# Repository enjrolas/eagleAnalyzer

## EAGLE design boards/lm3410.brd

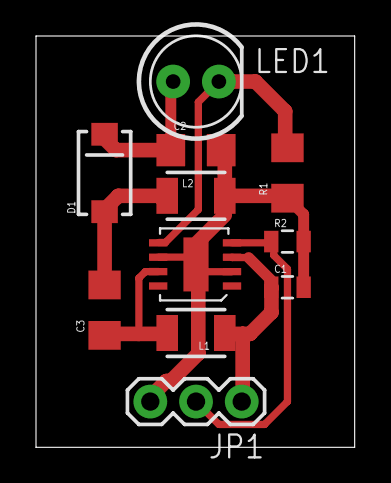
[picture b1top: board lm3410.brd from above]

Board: 2 copper layers, 17.7 x 22.9 mm, 11 parts (0 on the bottom side), 7 nets.

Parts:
C1: 10uF; 0805
C2: 10uF; 1206
C3: 2.2uF; 1206
D1: DIODE-SCHOTTKY_; SMA-DIODE
JP1: 1X03
L1, L2: 4.7uH; 1210
LED1: LED5MM
R1: 0.2; 1206
R2: 100k; 0805
U$1: LM3410-MSOP-8; MSOP-8

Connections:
DIM: JP1.2, R2.1, U$1.4
GND: C1.2, C2.2, JP1.3, L2.2, R1.1, R2.2, U$1.2, U$1.6, U$1.9
unnamed: LED1.K, R1.2, U$1.5
unnamed: C3.1, L1.2, U$1.7
unnamed: C3.2, D1.A, L2.1
unnamed: C2.1, D1.C, LED1.A
VCC: C1.1, JP1.1, L1.1, U$1.3

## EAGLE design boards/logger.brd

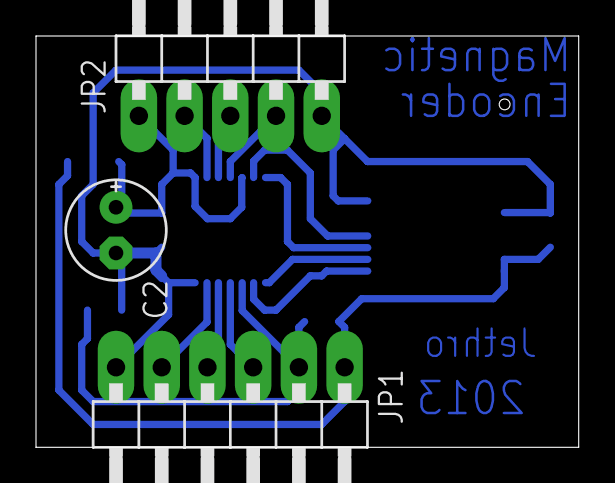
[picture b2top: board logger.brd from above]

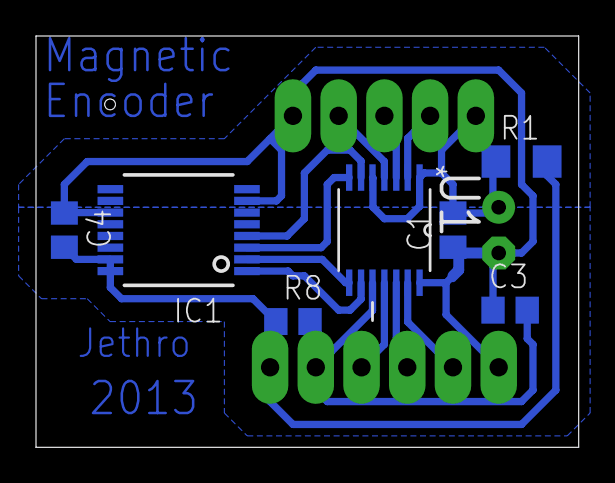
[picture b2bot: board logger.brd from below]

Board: 2 copper layers, 30.2 x 22.9 mm, 10 parts (7 on the bottom side), 14 nets.

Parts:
C1, C3, C4: C0805
C2: E2,5-6E
IC1: AS5040; SSOP16
JP1: 1X06/90
JP2: 1X05/90
R1: R1206
R8: R0805
U1: MSP430G2352IPW14; SOP65P640X120-14N

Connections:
+3V3: C1.2, C2.+, JP2.1, R1.1, U1.1, U1.5
GND: C1.1, C2.-, C3.1, C4.1, IC1.7, IC1.11, JP1.6, JP2.5, U1.14
unnamed: JP1.3, U1.11
unnamed: JP2.3, U1.3
unnamed: JP1.4, U1.12
unnamed: IC1.4, U1.6
unnamed: IC1.3, U1.7
unnamed: C4.2, IC1.15, IC1.16, JP1.1, R1.2, R8.1
unnamed: JP1.5, U1.13
unnamed: IC1.2, U1.8
unnamed: IC1.1, U1.9
unnamed: JP2.2, U1.2
unnamed: C3.2, JP1.2, R8.2, U1.10
unnamed: JP2.4, U1.4

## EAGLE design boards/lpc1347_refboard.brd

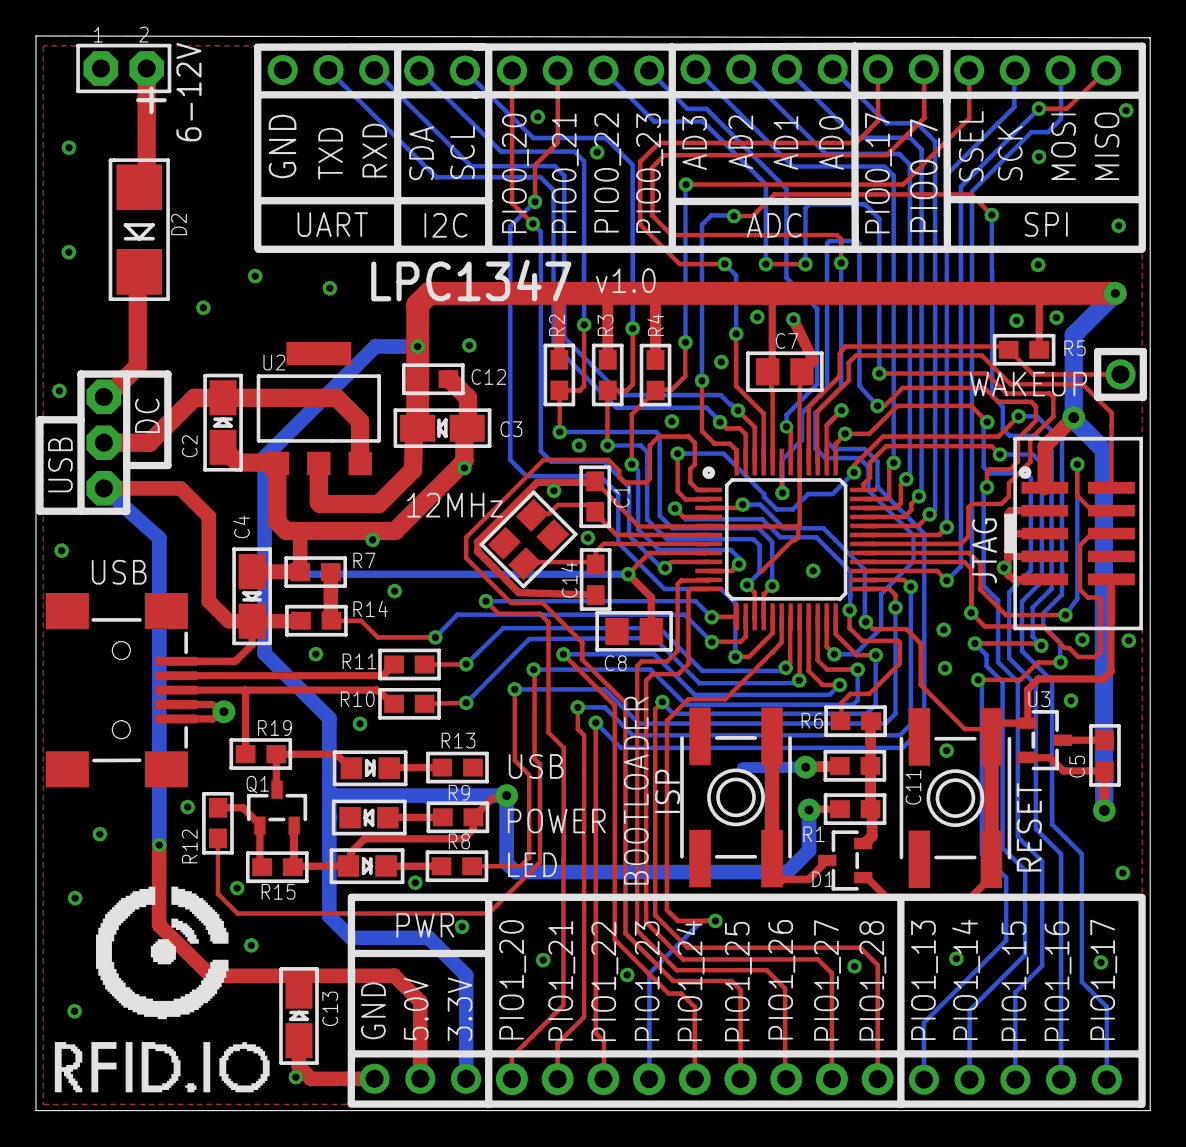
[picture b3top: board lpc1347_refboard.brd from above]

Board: 2 copper layers, 61.9 x 59.7 mm, 54 parts (0 on the bottom side), 59 nets.

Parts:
BTN1: Reset; EVQ-Q2
BTN2: ISP; EVQ-Q2
C1, C14: 16pF; 0603
C2, C3, C4, C13: 10µF; EIA3216-18/A-R
C5, C11, C12: 0.1µF; 0603
C7, C8: 10µF; 0805
CN1: USBMINIB; USB-MINIB
D1: BAT54C; SOT23-R
D2: MULTICOMPSS12; SMADIODE
JP1: PWR; 1X03_ROUND
JP2: ADC; 1X04_ROUND
JP3: SPI; 1X04_ROUND
JP4: I2C; 1X02_ROUND
JP5: UART; 1X03_ROUND
JP6: WAKEUP; 1X01_ROUND
JP7: 1X04_ROUND
JP9: 1X05_ROUND
JP10: JUMPER2
JP11: 1X09_ROUND_70
JP12: POWERSOURCE; JUMPER3
JP13: 1X02_ROUND
JTAG1: JTAG; 2X05_1.27MM_SMT
LED1: POWER; CHIPLED_0805
LED2: 2mA; CHIPLED_0805
LED3: USB; CHIPLED_0805
Q1: MMBT2907A; SOT23-R
R1: 20K; 0603
R2, R3, R4, R5, R14, R15: 10K; 0603
R6: 1K; 0603
R7: 100K; 0603
R8: 1.0K; 0603
R9, R13: 150; 0603
R10, R11: 33; 0603
R12: 2K; 0603
R19: 1.5K; 0603
U2: LM1117(3.3); SOT223-R
U3: MCP130T; SOT23-R
U4: LPC1347FBD48; LQFP48
U$23: RFID_IO_LOGO_1X1
Y2: 12MHz; CRYSTAL_3.2X2.5

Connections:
3.3V: C3.+, C5.1, C7.1, C8.1, C12.1, JP1.1, JTAG1.1, LED2.A, Q1.2, R1.2, R2.2, R3.2, R4.2, R5.2, R9.1, R15.1, U2.2, U3.2, U4.8, U4.44
5.0V: C4.+, C13.+, CN1.VBUS, JP1.2, JP12.1, R14.1
GND: BTN1.A, BTN1.A', BTN2.A, BTN2.A', C1.1, C2.-, C3.-, C4.-, C5.2, C7.2, C8.2, C11.2, C12.2, C13.-, C14.1, CN1.GND, CN1.ID, JP1.3, JP5.1, JP10.1, JTAG1.3, JTAG1.5, JTAG1.7, JTAG1.9, LED1.C, R7.1, R13.1, U2.1, U3.3, U4.5, U4.41
unnamed: LED2.C, R8.1
unnamed: C2.+, JP12.2, U2.3
unnamed: D2.A, JP10.2
unnamed: BTN2.B, BTN2.B', D1.3
unnamed: CN1.D+, R10.1, R19.2
unnamed: Q1.1, R12.1, R15.2
unnamed: C11.1, D1.2, R1.1, R6.1
unnamed: LED1.A, R9.2
unnamed: LED3.C, R13.2
unnamed: CN1.D-, R11.1
unnamed: LED3.A, Q1.3, R19.1
PIO0_0/RESET: BTN1.B, BTN1.B', D1.1, JTAG1.10, U3.1, U4.3
PIO0_1/ISP: R6.2, U4.4
PIO0_2/SSEL: JP3.4, R4.1, U4.10
PIO0_3/USBVBUS: R7.2, R14.2, U4.14
PIO0_4/SCL: JP4.1, R3.1, U4.15
PIO0_5/SDA: JP4.2, R2.1, U4.16
PIO0_6/USBCONNECT: R12.2, U4.22
PIO0_7: JP13.2, U4.23
PIO0_8/MISO: JP3.1, U4.27
PIO0_9/MOSI/SWO: JP3.2, JTAG1.6, U4.28
PIO0_10/SWCLK: JTAG1.4, U4.29
PIO0_11/AD0: JP2.1, U4.32
PIO0_12/AD1: JP2.2, U4.33
PIO0_13/AD2: JP2.3, U4.34
PIO0_14/AD3: JP2.4, U4.35
PIO0_15/SWDIO: JTAG1.2, U4.39
PIO0_16/WAKEUP: JP6.1, R5.1, U4.40
PIO0_17: JP13.1, U4.45
PIO0_18/RXD: JP5.3, U4.46
PIO0_19/TXD: JP5.2, U4.47
PIO0_20: JP7.4, U4.9
PIO0_21: JP7.3, U4.17
PIO0_22: JP7.2, U4.30
PIO0_23: JP7.1, U4.42
PIO1_13: JP9.1, U4.36
PIO1_14: JP9.2, U4.37
PIO1_15: JP9.3, U4.43
PIO1_16: JP9.4, U4.48
PIO1_19: JP9.5, U4.2
PIO1_20: JP11.1, U4.13
PIO1_21: JP11.2, U4.26
PIO1_22: JP11.3, U4.38
PIO1_23: JP11.4, U4.18
PIO1_24: JP11.5, U4.21
PIO1_25: JP11.6, U4.1
PIO1_26: JP11.7, U4.11
PIO1_27: JP11.8, U4.12
PIO1_28: JP11.9, U4.24
PIO1_29/SCK: JP3.3, U4.31
PIO1_31/LED: R8.2, U4.25
USBD+: R10.2, U4.20
USBD-: R11.2, U4.19
VCC: D2.C, JP12.3
XTALIN: C1.2, U4.6, Y2.2
XTALOUT: C14.2, U4.7, Y2.1

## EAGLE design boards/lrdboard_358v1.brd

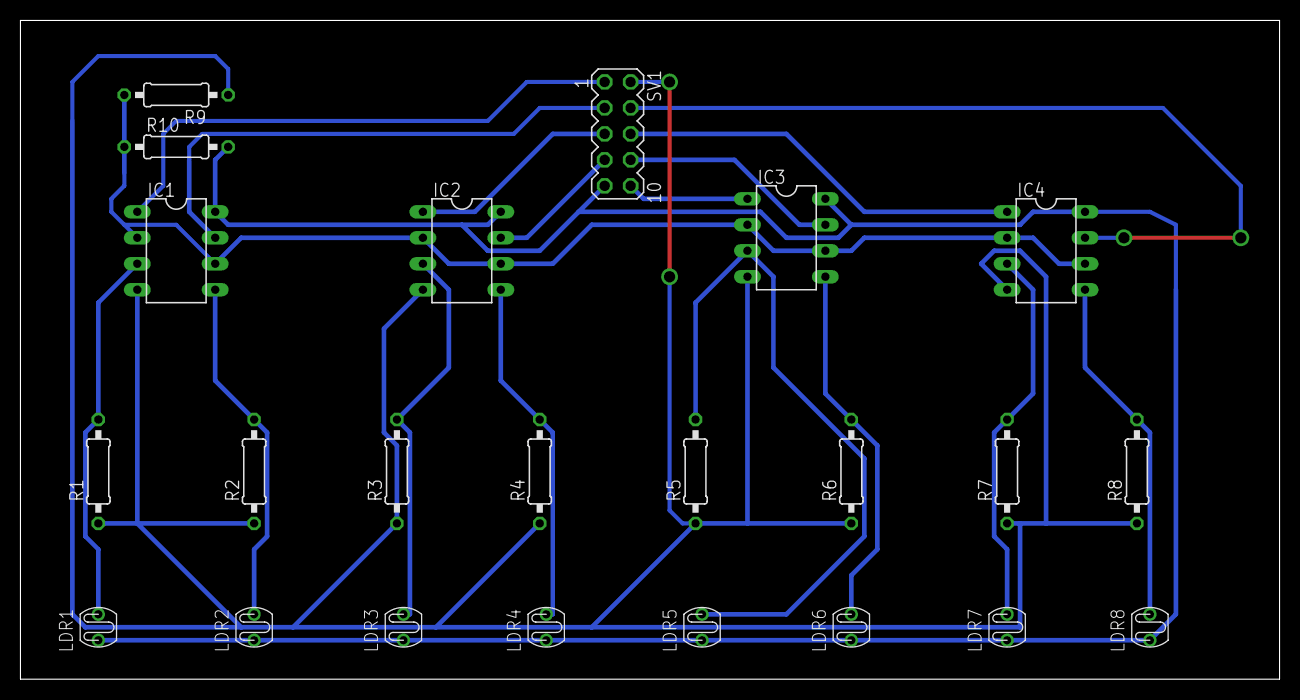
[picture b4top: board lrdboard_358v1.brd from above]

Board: 2 copper layers, 123.2 x 64.4 mm, 23 parts (0 on the bottom side), 19 nets.

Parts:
IC1, IC2, IC3, IC4: LM358N; DIL08
LDR1, LDR2, LDR3, LDR4, LDR5, LDR6, LDR7, LDR8: CDSLDR3MM; LDR3MM
R1, R2, R3, R4, R5, R6, R7, R8, R9, R10: 0207/10
SV1: MA05-2

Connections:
1: IC1.3, LDR1.P$2, R1.2
2: IC1.5, LDR2.P$2, R2.2
3: IC2.3, LDR3.P$2, R3.2
4: IC2.5, LDR4.P$2, R4.2
5: IC3.3, LDR5.P$2, R5.2
6: IC3.5, LDR6.P$2, R6.2
7: IC4.3, LDR7.P$2, R7.2
8: IC4.5, LDR8.P$2, R8.2
+5V: IC1.8, IC2.8, IC3.8, IC4.8, LDR1.P$1, LDR2.P$1, LDR3.P$1, LDR4.P$1, LDR5.P$1, LDR6.P$1, LDR7.P$1, LDR8.P$1, R10.2, SV1.9
GND: IC1.4, IC2.4, IC3.4, IC4.4, R1.1, R2.1, R3.1, R4.1, R5.1, R6.1, R7.1, R8.1, R9.1, SV1.2
MID: IC1.2, IC1.6, IC2.2, IC2.6, IC3.2, IC3.6, IC4.2, IC4.6, R9.2, R10.1
OUT1: IC1.1, SV1.1
OUT2: IC1.7, SV1.3
OUT3: IC2.1, SV1.5
OUT4: IC2.7, SV1.7
OUT5: IC3.1, SV1.10
OUT6: IC3.7, SV1.8
OUT7: IC4.1, SV1.6
OUT8: IC4.7, SV1.4

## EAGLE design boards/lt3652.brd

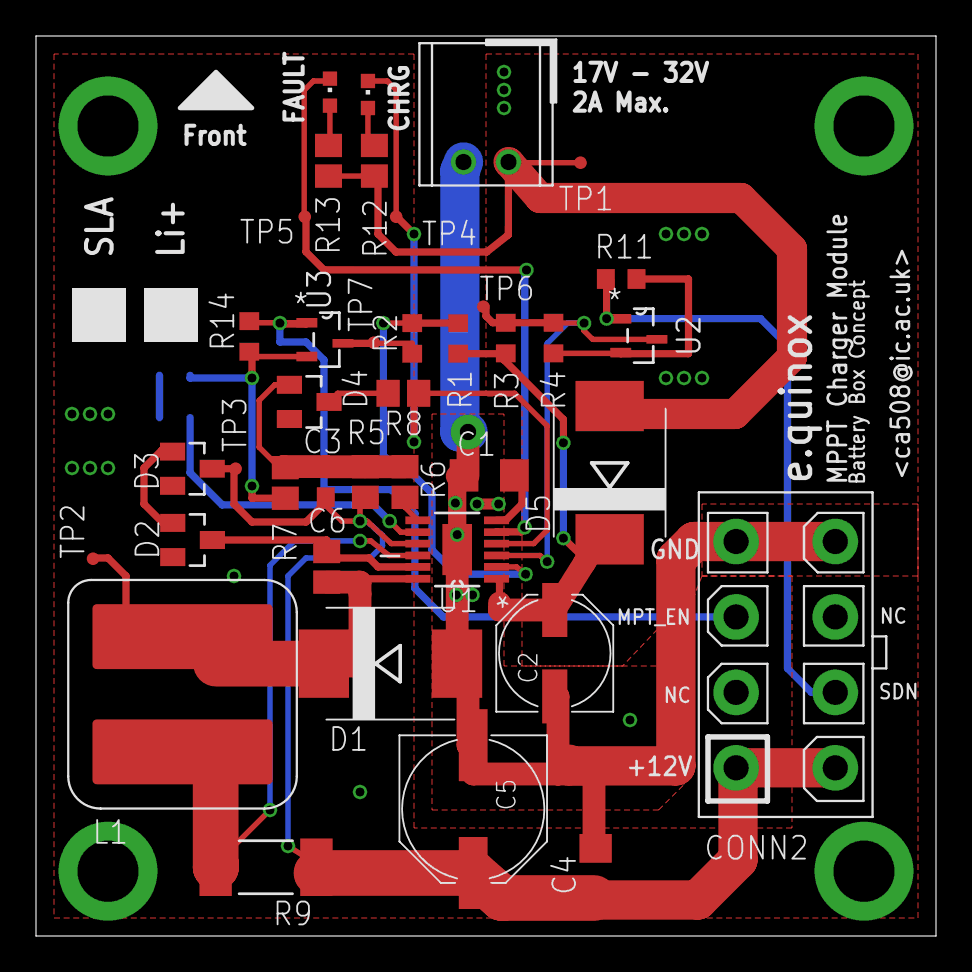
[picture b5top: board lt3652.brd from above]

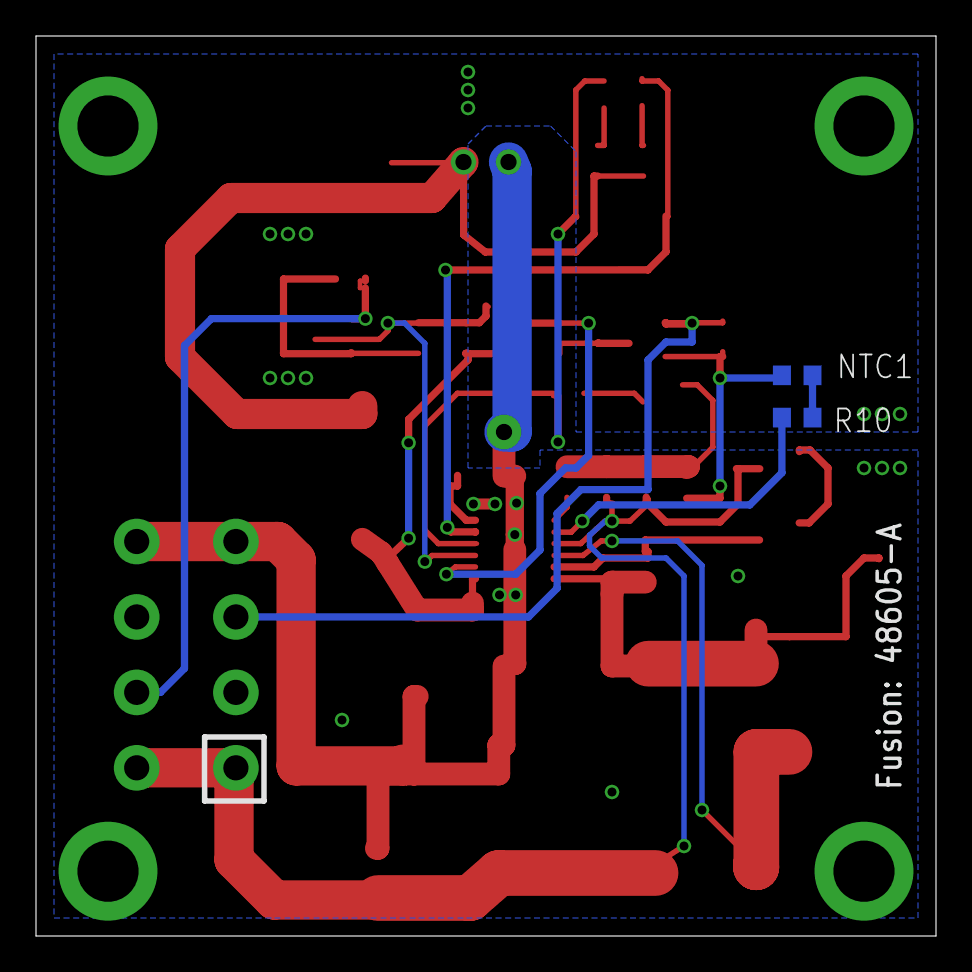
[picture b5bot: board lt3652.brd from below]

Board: 2 copper layers, 50.0 x 50.0 mm, 41 parts (2 on the bottom side), 23 nets.

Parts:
C1: 4.7uF; C1206
C2: 33uF; PANASONIC_D
C3: 50pF; C0603
C4: 10uF; C1206
C5: 100uF; PANASONIC_F
C6: 1uF; C0805
CONN1: 22-05-7025
CONN2: 39-28-1083
D1, D5: MBRS340T3; SMC
D2: PMBD914; SOT23
D3: BZX84C6V2L; SOT23
D4: BAW56; SOT23
L1: SDR1006-220ML; SDR1006
LED1: GREEN; CHIPLED_0603
LED2: RED; CHIPLED_0603
NTC1: 10k; R0603
R1: 499k; R0603
R2: 100k; R0603
R3: 0; R0603
R4: DNP; R0603
R5: 309k; R0805
R6: 174k; R0805
R7: 100k; R0805
R8: 1M; R0805
R9: 0.06; R2512
R10: 910; R0603
R11, R14: 2.7k; R0603
R12, R13: 4.7k; R0805
TP1, TP2, TP3, TP4, TP5, TP6, TP7: TPTP07R; TP07R
U1: LT3652EMSEPBF; SOP65P490X110-13N
U2, U3: 2N7002E; SOT95P230X110-3N

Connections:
0V: C1.2, C2.-, C4.2, C5.-, CONN1.2, CONN2.P$4, CONN2.P$8, D1.A, NTC1.1, R4.1, R7.2, R11.1, R14.1, U1.13, U2.2, U3.2
!CHRG: LED1.C, R8.2, TP4.TP, U1.4
!MPPT!: R2.1, TP7.TP, U3.3
!SHDN!: R3.1, R4.2, TP6.TP, U1.3, U2.3
+12V: C3.1, C4.1, C5.+, CONN2.P$1, CONN2.P$5, D3.3, R5.2, R9.1, TP3.TP, U1.9
CHG_VIN: C2.+, D5.C, R1.2, R3.2, U1.1
MPPT_EN: CONN2.P$3, R14.2, U3.1
unnamed: R1.1, R2.2, U1.2
unnamed: C6.2, D1.C, L1.P$1, TP2.TP, U1.12
unnamed: C1.1, U1.6
unnamed: C6.1, D2.3, U1.11
unnamed: R10.2, U1.8
unnamed: D2.1, D3.1
unnamed: L1.P$2, R9.2, U1.10
unnamed: C3.2, D4.1, R5.1, R6.1, R7.1
unnamed: D4.3, R8.1
unnamed: LED2.C, TP5.TP, U1.5
unnamed: NTC1.2, R10.1
unnamed: LED1.A, R12.1
unnamed: LED2.A, R13.1
SHDN: CONN2.P$6, R11.2, U2.1
VCC: CONN1.1, D5.A, R12.2, R13.2, TP1.TP
VFB: R6.2, U1.7

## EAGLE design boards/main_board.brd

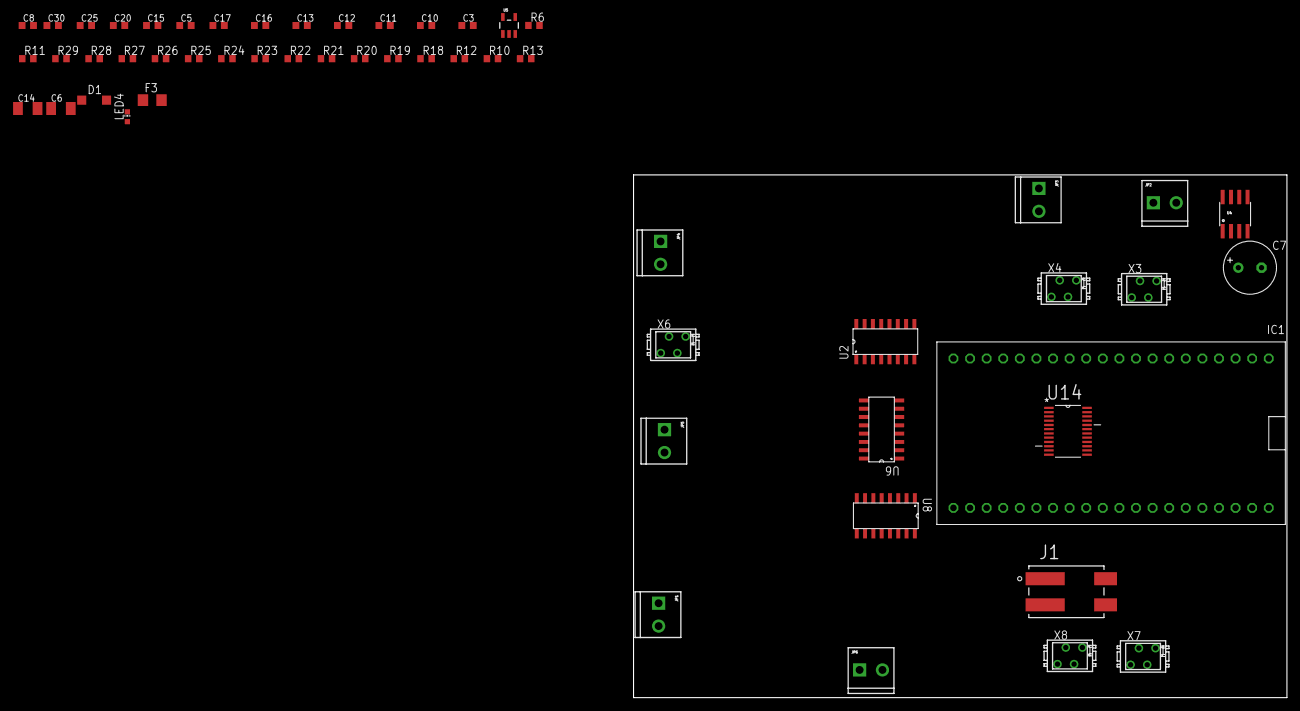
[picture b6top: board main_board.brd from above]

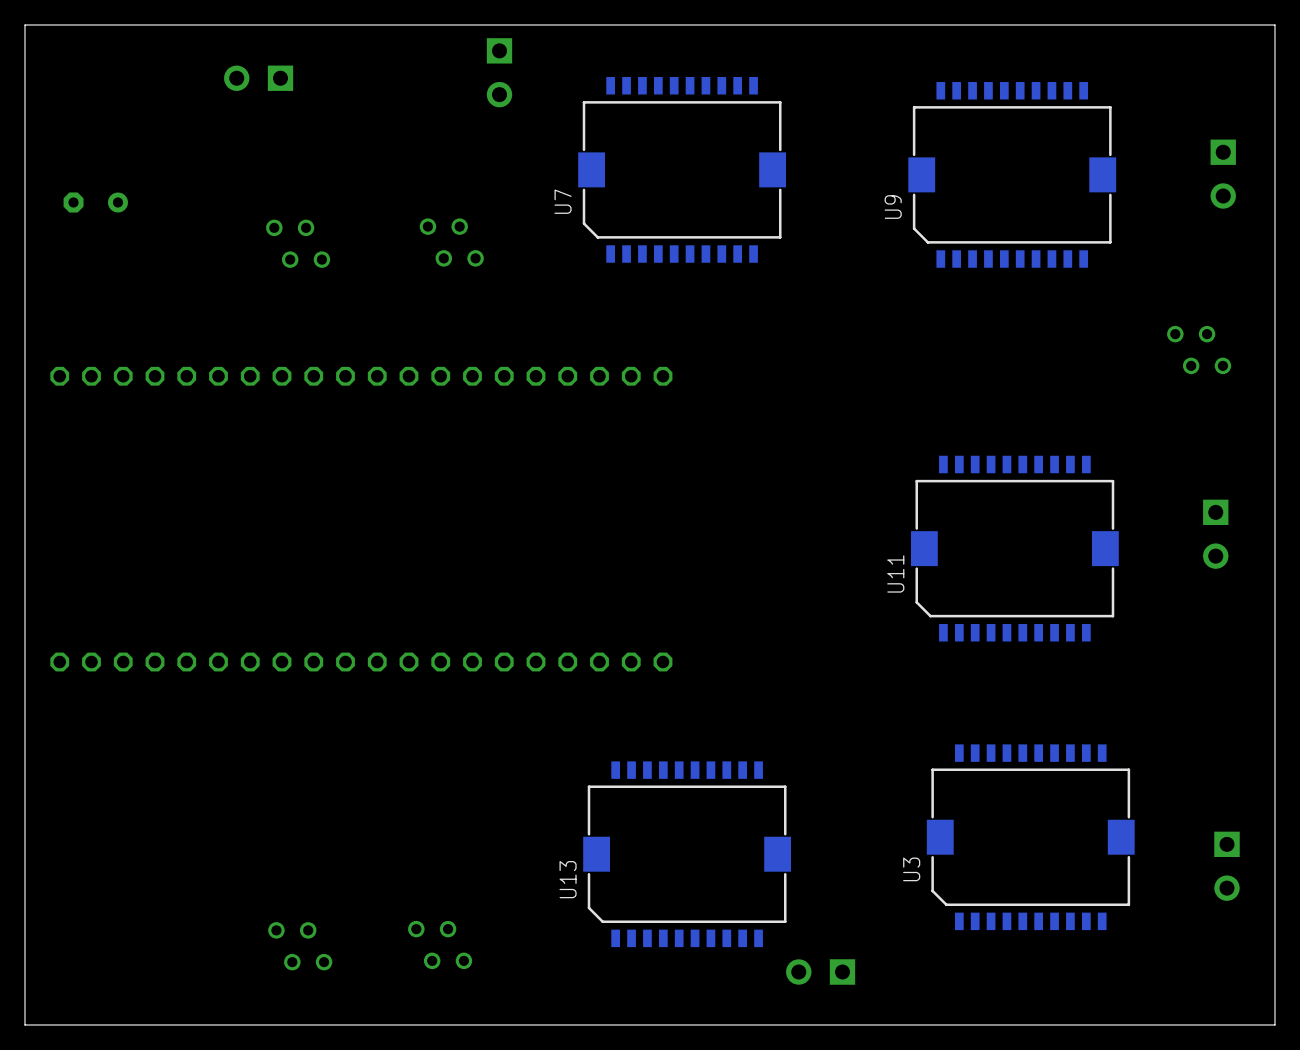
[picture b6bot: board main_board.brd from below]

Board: 2 copper layers, 100.0 x 80.0 mm, 60 parts (5 on the bottom side), 83 nets, no tracks yet.

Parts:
C3, C10, C11, C12, C13, C16, C17: 100nF; C0603K
C5, C15, C20, C25, C30: 33nF; C0603K
C6, C14: 10uF; C1206K
C7: 470uF-16V; E3,5-8
C8: 1uF; C0603K
D1: 12V; SOD123
F3: FUSE_5A; R1206
IC1: MBED_MICROCONTROLLER; DIL40_0.9
J1: 2060-402; WAGO_2060-402
JP1, JP3, JP4, JP5, JP6: MOTOR; SCREWTERMINAL-3.5MM-2
JP2: PWR; SCREWTERMINAL-3.5MM-2
LED4: CHIP-LED0603
R6: 1k; R0603
R10, R11, R12, R18, R19, R20, R21, R22, R23, R24, R25, R26, R27, R28, R29: 10k; R0603
R13: 100k; R0603
U2, U6, U8: SI8460AA-B-IS1; SOIC-16
U3, U7, U9, U11, U13: MC33887-HSOP; HSOP
U4: NFET-SOIC8; SO08
U5: LDO; SOT23-5
U14: PCF8575PWE4; SOP65P640X120-24N
X3: ENC1; MICROMATCH-4
X4: ENC2; MICROMATCH-4
X6: ENC3; MICROMATCH-4
X7: ENC4; MICROMATCH-4
X8: ENC5; MICROMATCH-4

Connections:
+3V3: IC1.40, U14.24
+5V: C6.1, C11.1, C13.1, C17.1, R6.2, R11.2, R12.2, R19.2, R20.2, R22.2, R23.2, R25.2, R26.2, R28.2, R29.2, U2.16, U5.5, U6.16, U8.16
+12V: C8.1, F3.1, U3.4, U3.5, U3.16, U5.1, U5.3, U7.4, U7.5, U7.16, U9.4, U9.5, U9.16, U11.4, U11.5, U11.16, U13.4, U13.5, U13.16
DIR1_1: U2.3, U14.4
DIR1_1_D: U2.14, U3.3
DIR1_2: U2.4, U14.5
DIR1_2_D: U2.13, U3.19
DIR2_1: U2.6, U14.6
DIR2_1_D: U2.11, U7.3
DIR2_2: U2.7, U14.7
DIR2_2_D: U2.10, U7.19
DIR3_1: U6.3, U14.8
DIR3_1_D: U6.14, U9.3
DIR3_2: U6.4, U14.9
DIR3_2_D: U6.13, U9.19
DIR4_1: U6.6, U14.10
DIR4_1_D: U6.11, U11.3
DIR4_2: U6.7, U14.11
DIR4_2_D: U6.10, U11.19
DIR5_1: U8.3, U14.13
DIR5_1_D: U8.14, U13.3
DIR5_2: U8.4, U14.14
DIR5_2_D: U8.13, U13.19
ENC1A: IC1.8, X3.3
ENC1B: IC1.11, X3.4
ENC2A: IC1.12, X4.3
ENC2B: IC1.15, X4.4
ENC3A: IC1.16, X6.3
ENC3B: IC1.17, X6.4
ENC4A: IC1.18, X7.3
ENC4B: IC1.26, X7.4
ENC5A: IC1.27, X8.3
ENC5B: IC1.28, X8.4
EXTEND_SCL: IC1.10, U14.22
EXTEND_SDA: IC1.9, U14.23
FAUL1T_D: R12.1, U3.2
FAULT1_D: R20.1, U7.2
FAULT3_D: R23.1, U9.2
FAULT4_D: R26.1, U11.2
FAULT5_D: R29.1, U13.2
GND: C10.2, C12.2, C16.2, IC1.1, U2.8, U6.8, U8.8, U14.2, U14.3, U14.12, U14.21, X3.1, X4.1, X6.1, X7.1, X8.1
GNDA: C3.2, C5.2, C6.2, C7.-, C8.2, C11.2, C13.2, C14.2, C15.2, C17.2, C20.2, C25.2, C30.2, D1.A, LED4.C, R10.1, R18.1, R21.1, R24.1, R27.1, U2.9, U3.1, U3.9, U3.10, U3.11, U3.12, U3.SL1, U3.SL2, U4.1, U4.2, U4.3, U5.2, U6.9, U7.1, U7.9, U7.10, U7.11, U7.12, U7.SL1, U7.SL2, U8.9, U9.1, U9.9, U9.10, U9.11, U9.12, U9.SL1, U9.SL2, U11.1, U11.9, U11.10, U11.11, U11.12, U11.SL1, U11.SL2, U13.1, U13.9, U13.10, U13.11, U13.12, U13.SL1, U13.SL2
unnamed: C3.1, U5.4
unnamed: LED4.A, R6.1
unnamed: C5.1, U3.17
unnamed: R11.1, U3.20
unnamed: R10.2, U3.18
unnamed: D1.C, R13.1, U4.4
unnamed: JP2.1, U4.5, U4.6, U4.7, U4.8
unnamed: JP1.2, U3.6, U3.7
unnamed: JP1.1, U3.14, U3.15
unnamed: C7.+, C14.1, F3.2, JP2.2, R13.2
unnamed: C15.1, U7.17
unnamed: R19.1, U7.20
unnamed: R18.2, U7.18
unnamed: JP3.2, U7.6, U7.7
unnamed: JP3.1, U7.14, U7.15
unnamed: C20.1, U9.17
unnamed: R22.1, U9.20
unnamed: R21.2, U9.18
unnamed: JP4.2, U9.6, U9.7
unnamed: JP4.1, U9.14, U9.15
unnamed: C25.1, U11.17
unnamed: R25.1, U11.20
unnamed: R24.2, U11.18
unnamed: JP5.2, U11.6, U11.7
unnamed: JP5.1, U11.14, U11.15
unnamed: C30.1, U13.17
unnamed: R28.1, U13.20
unnamed: R27.2, U13.18
unnamed: JP6.2, U13.6, U13.7
unnamed: JP6.1, U13.14, U13.15
PWM1: IC1.21, U2.2
PWM1_D: U2.15, U3.13
PWM2: IC1.22, U2.5
PWM2_D: U2.12, U7.13
PWM3: IC1.23, U6.2
PWM3_D: U6.15, U9.13
PWM4: IC1.24, U6.5
PWM4_D: U6.12, U11.13
PWM5: IC1.25, U8.2
PWM5_D: U8.15, U13.13
VCC: C10.1, C12.1, C16.1, IC1.2, U2.1, U6.1, U8.1, X3.2, X4.2, X6.2, X7.2, X8.2

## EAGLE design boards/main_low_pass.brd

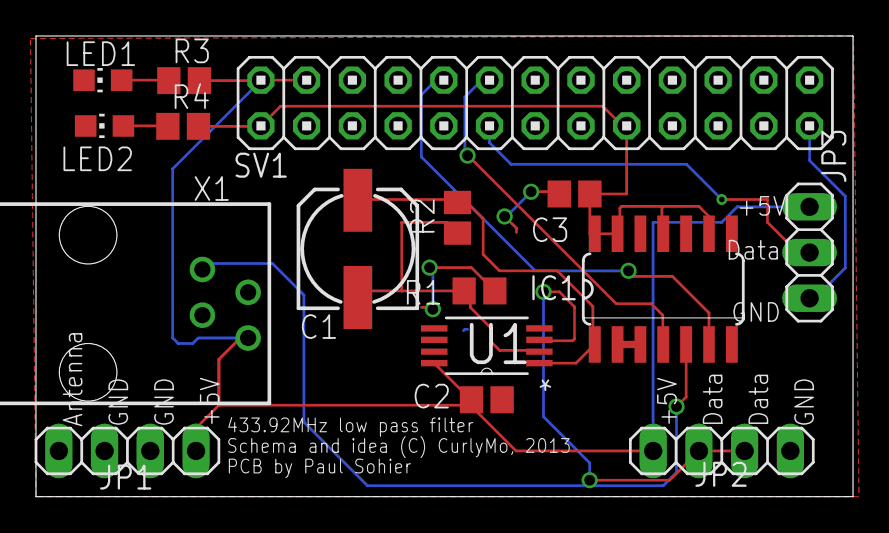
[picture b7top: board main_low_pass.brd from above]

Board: 2 copper layers, 45.4 x 25.6 mm, 16 parts (0 on the bottom side), 13 nets.

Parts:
C1: 15u; 153CLV-0605
C2, C3: C0805
IC1: 74HC14D; SO14
JP1, JP2: 1X04
JP3: 1X03
LED1, LED2: CHIP-LED0805
R1, R2, R3, R4: R0805
SV1: 2X13
U1: SOP65P640X120-8N
X1: 14867

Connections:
GND: C2.2, C3.2, IC1.7, JP1.2, JP1.3, JP2.4, JP3.1, LED1.C, LED2.C, R1.1, SV1.6, SV1.9, SV1.14, SV1.20, SV1.25, U1.4, X1.3
unnamed: JP2.2, JP2.3, U1.3
unnamed: C1.-, R1.2, R2.1, U1.2
unnamed: IC1.2, IC1.3
unnamed: IC1.5, X1.1
unnamed: JP3.2, SV1.11
unnamed: C2.1, JP1.4, JP2.1, JP3.3, R3.2, SV1.2, SV1.4, U1.8, X1.4
unnamed: C1.+, IC1.1, R2.2, U1.1
unnamed: LED1.A, R3.1
unnamed: LED2.A, R4.1
unnamed: IC1.4, SV1.12
unnamed: IC1.6, SV1.10
VCC: C3.1, IC1.9, IC1.11, IC1.13, IC1.14, R4.2, SV1.1, SV1.17

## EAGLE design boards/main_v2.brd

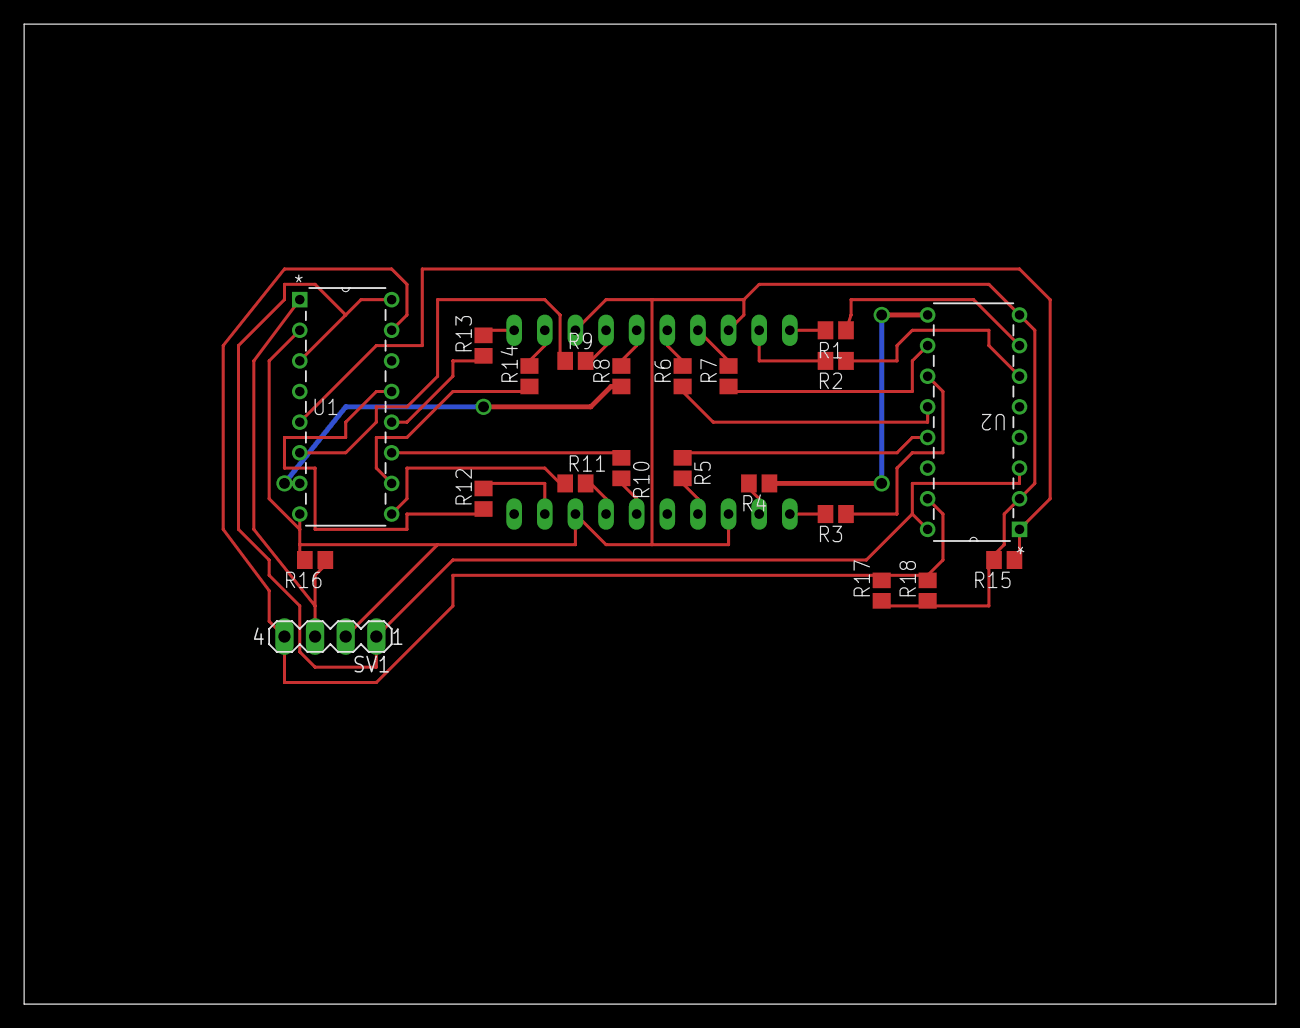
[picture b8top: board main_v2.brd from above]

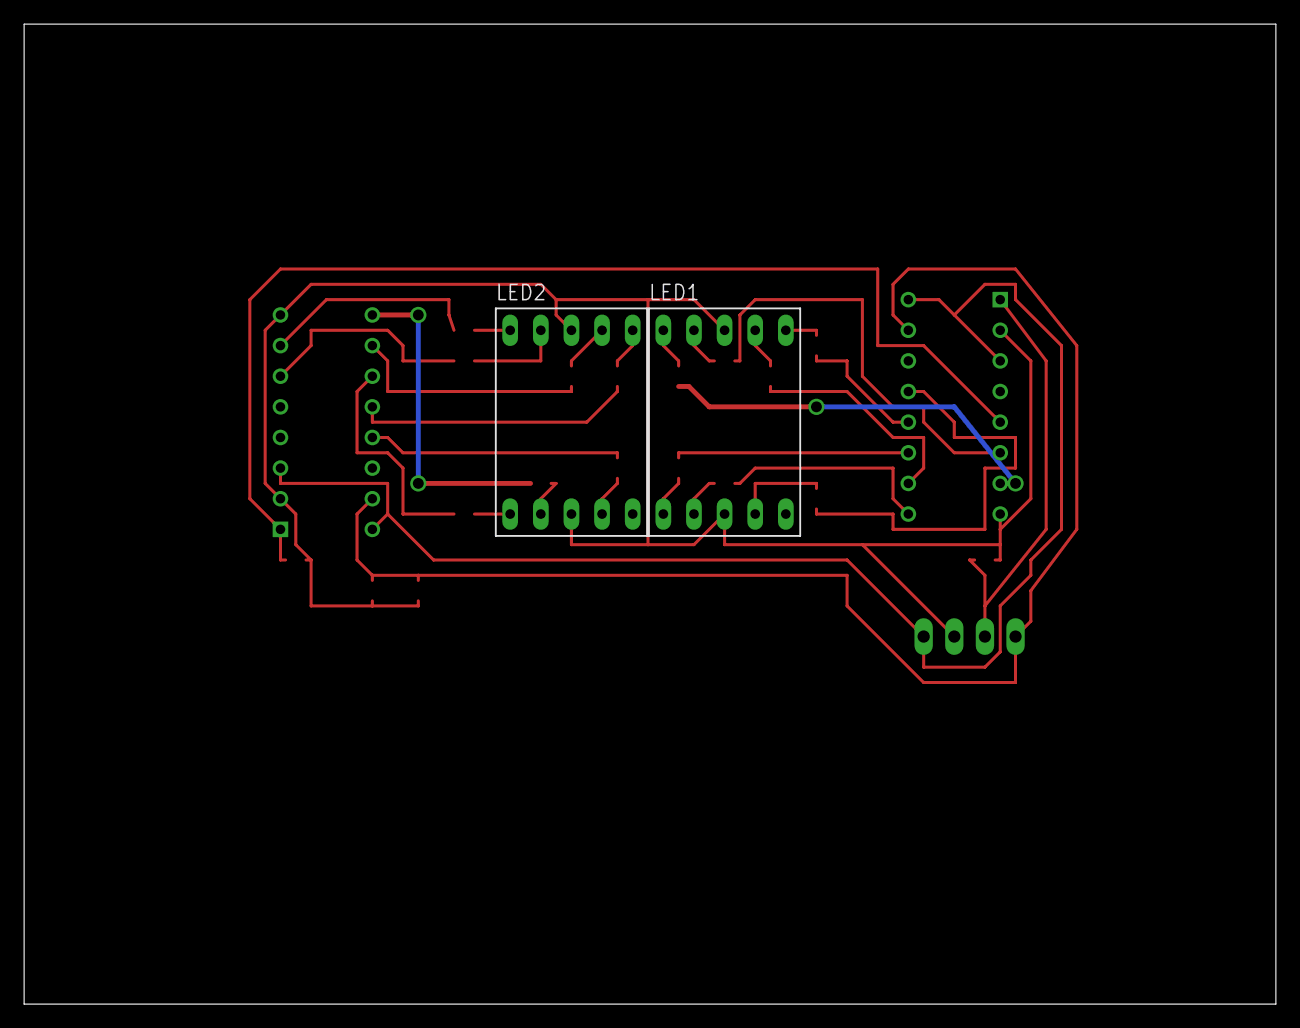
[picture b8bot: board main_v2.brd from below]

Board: 2 copper layers, 103.8 x 81.3 mm, 23 parts (2 on the bottom side), 33 nets.

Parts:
LED1, LED2: 7-SEG_SA56-11; SA56-11
R1, R2, R3, R4, R5, R6, R7, R8, R9, R10, R11, R12, R13, R14: 220; R0805
R15, R16, R17, R18: 10K; R0805
SV1: +5, 0, clock, reset; MA04-1
U1, U2: CD4026B_N_16; N16

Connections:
unnamed: LED2.10, R1.2
unnamed: LED2.9, R2.2
unnamed: LED2.1, R3.2
unnamed: LED2.2, R4.2
unnamed: LED2.4, R5.2
unnamed: LED2.6, R6.2
unnamed: LED2.7, R7.2
unnamed: SV1.1, U1.3, U1.16, U2.3, U2.16
unnamed: LED1.3, LED1.8, LED2.3, LED2.8, R15.2, R16.2, R17.1, R18.1, SV1.2, U1.2, U1.8, U2.2, U2.8
unnamed: LED1.10, R8.2
unnamed: LED1.9, R9.2
unnamed: LED1.1, R10.2
unnamed: LED1.2, R11.2
unnamed: LED1.4, R12.2
unnamed: LED1.6, R13.2
unnamed: LED1.7, R14.2
unnamed: R16.1, SV1.3, U1.1
unnamed: R7.1, U2.10
unnamed: R6.1, U2.12
unnamed: R5.1, U2.13
unnamed: R4.1, U2.9
unnamed: R3.1, U2.11
unnamed: R2.1, U2.6
unnamed: R1.1, U2.7
unnamed: R17.2, R18.2, SV1.4, U1.15, U2.15
unnamed: R15.1, U1.5, U2.1
unnamed: R9.1, U1.6
unnamed: R8.1, U1.7
unnamed: R12.1, U1.13
unnamed: R13.1, U1.12
unnamed: R10.1, U1.11
unnamed: R14.1, U1.10
unnamed: R11.1, U1.9

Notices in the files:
boards/lpc1347_refboard.brd:
(CC BY-SA 3.0)
parts and their libraries:
SparkFun-Passives: Licensing: CC v3.0 Share-Alike You are welcome to use this library for commercial purposes.
microbuilder: This work is placed in the public domain, and may be freely used for commercial and non-commercial work with the following conditions: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
